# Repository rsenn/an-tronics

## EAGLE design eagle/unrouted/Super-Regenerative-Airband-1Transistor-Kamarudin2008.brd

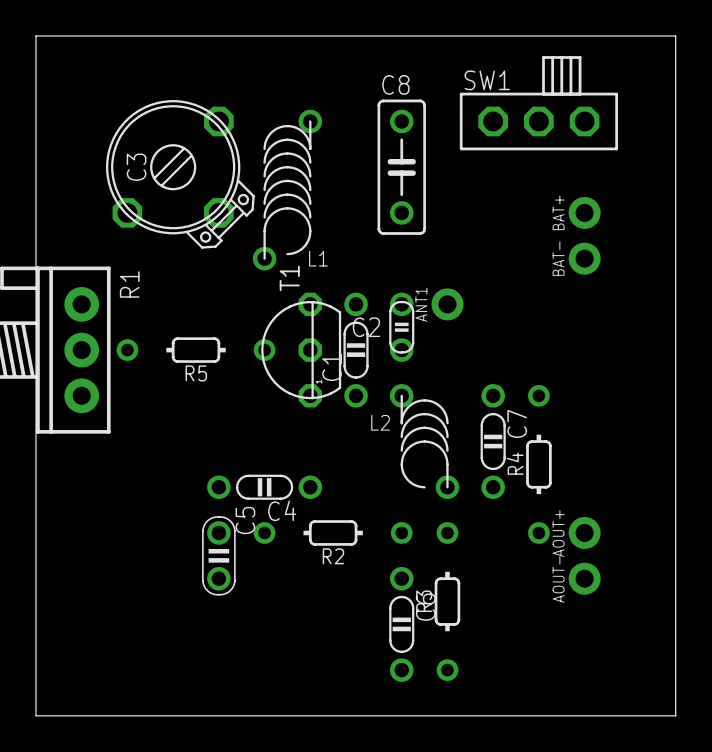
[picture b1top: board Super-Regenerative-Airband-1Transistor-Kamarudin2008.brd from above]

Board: 2 copper layers, 35.5 x 37.8 mm, 22 parts (0 on the bottom side), 12 nets, no tracks yet.

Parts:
ANT1: ANT; SPAD
AOUT+: SPAD
AOUT-: SPAD
BAT+: SPAD
BAT-: SPAD
C1: 6p; C050-020X036
C2: 2p; C025-015X024
C3: 15 - 140p; TRIM-2222-808
C4, C7: 470n; C050-020X036
C5: 1n; C025-020X036
C6: 1n; C050-020X036
C8: C050-025X075
L1: 6turns on d=0.7mm; L-04/7V-X
L2: L-SHORT02/5; L-04-5/6V
R1: 47k; POT
R2, R3: 12k; 0202/7
R4: 22k; 0202/7
R5: 68; 0202/7
SW1: SL-SW-1P-2T-H; SLSW-1P2T-H
T1: 2N3904; TO92

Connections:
GND: AOUT-.1, BAT-.1, C3.2, C5.2, C6.2, C8.2, R1.3, R3.2
unnamed: C1.2, L1.1, T1.3
unnamed: C1.1, C2.2, L2.1, T1.1
unnamed: C3.3, C8.1, L1.2, R1.1, SW1.3
unnamed: C4.2, C5.1, R5.2, T1.2
unnamed: ANT1.1, C2.1
unnamed: BAT+.1, SW1.1, SW1.2
unnamed: C4.1, R2.1
unnamed: C7.1, R4.1
unnamed: AOUT+.1, R4.2
unnamed: R1.2, R5.1
unnamed: C6.1, C7.2, L2.2, R2.2, R3.1

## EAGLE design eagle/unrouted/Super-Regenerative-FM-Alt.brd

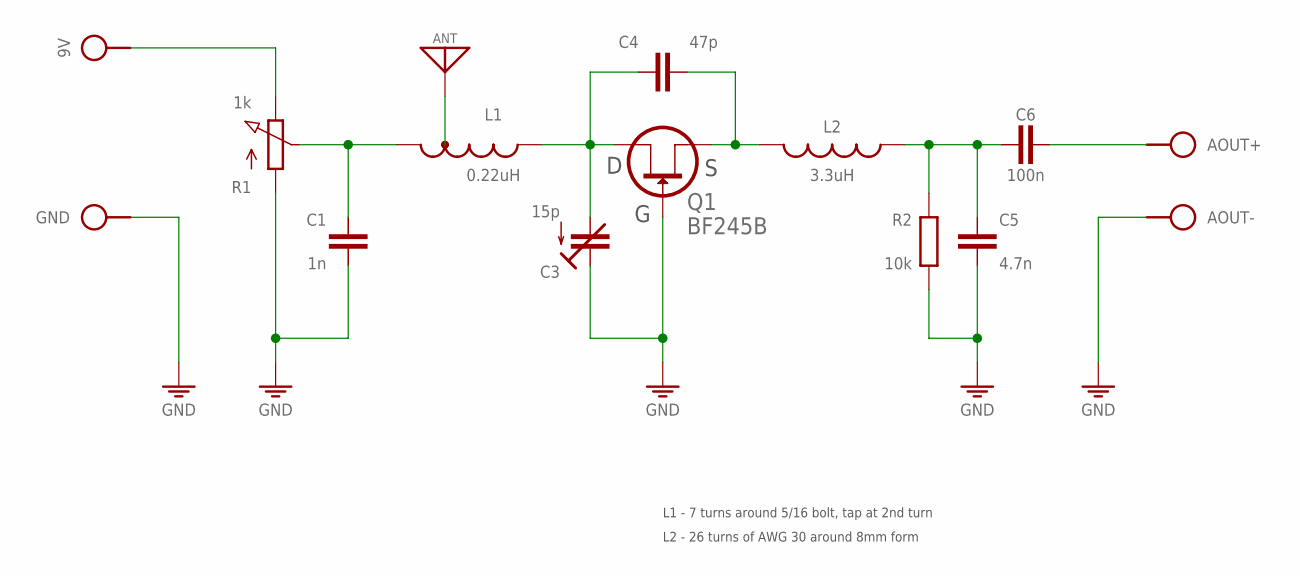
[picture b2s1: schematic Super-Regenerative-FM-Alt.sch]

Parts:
9V: SPAD
ANT: ANT; SPAD
AOUT+: SPAD
AOUT-: SPAD
C1: 1n; C050-020X036/V
C3: 15p; TRIM-2222-808
C4: 47p; C050-020X036
C5: 4.7n; C050-020X036
C6: 100n; C050-020X036
GND: SPAD
L1: 0.22uH; L-08/20V-TAP1
L2: 3.3uH; L-BODY
Q1: BF245B; TO92
R1: 1k; POT-V
R2: 10k; 0204/10

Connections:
GND: AOUT-.1, C1.2, C3.1 (E), C5.2, GND.1, Q1.1 (G), R1.A, R2.1
unnamed: 9V.1, R1.E
unnamed: C3.2 (A), C4.1, L1.2, Q1.3 (D)
unnamed: C1.1, L1.1, R1.S
unnamed: ANT.1, L1.T
unnamed: C4.2, L2.3 (2), Q1.2 (S)
unnamed: C5.1, C6.1, L2.2 (1), R2.2
unnamed: AOUT+.1, C6.2

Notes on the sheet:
L1 - 7 turns around 5/16 bolt, tap at 2nd turn
L2 - 26 turns of AWG 30 around 8mm form

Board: 2 copper layers, 15 parts (0 on the bottom side), 8 nets, no tracks yet.

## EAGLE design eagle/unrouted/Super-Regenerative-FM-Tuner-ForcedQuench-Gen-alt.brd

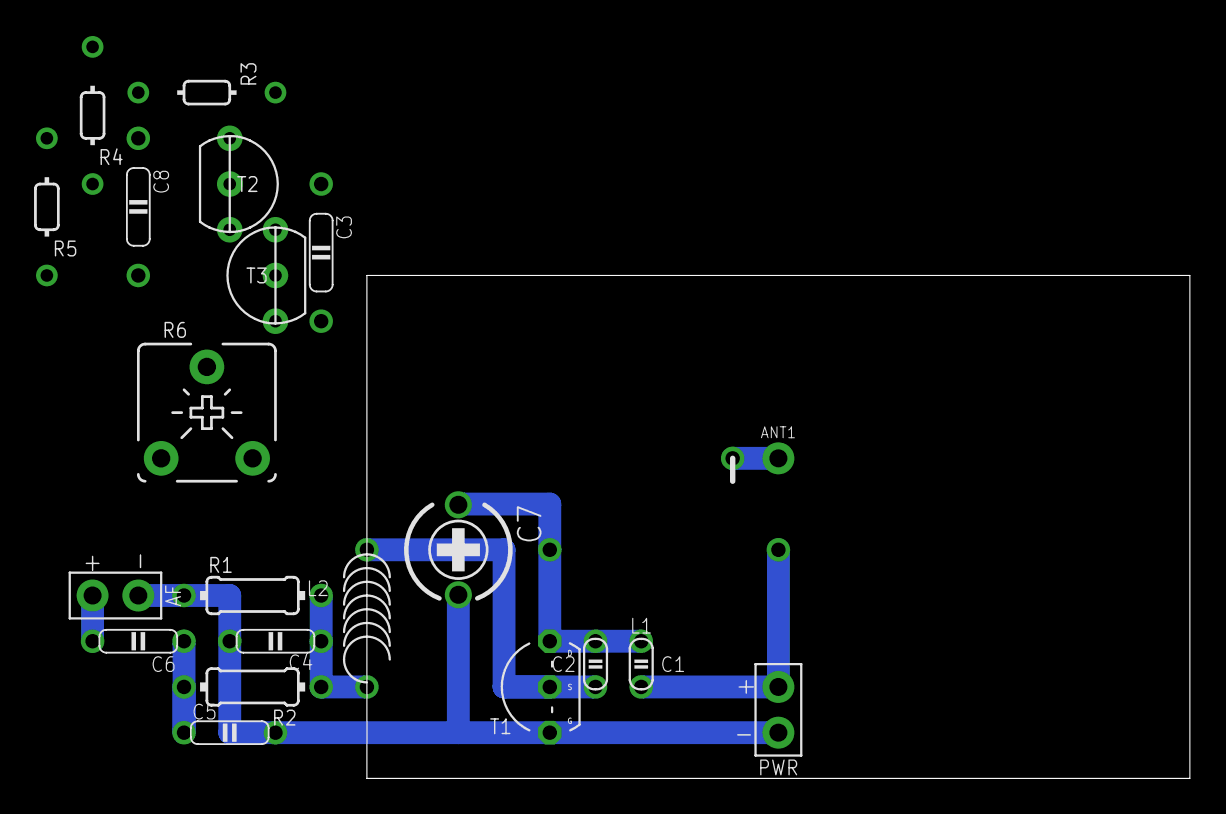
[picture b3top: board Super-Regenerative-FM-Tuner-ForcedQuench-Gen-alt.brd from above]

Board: 2 copper layers, 45.7 x 27.9 mm, 22 parts (0 on the bottom side), 12 nets.

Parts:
AF: SPAD+-+-; SPAD+-
ANT1: ANT; SPAD
C1: 20pF; C025-015X024
C2: 10pF; C025-015X024
C3, C8: 2.7nF; C0750-020X044
C4: 2.7nF; C050-020X044@1
C5: 10nF; C050-020X044@1
C6: 100nF; C050-020X044
C7: 0.04 - 6pF; CTRIMTZ03
L1: 0.1uH; L-08/12-TAP1
L2: 8.2uH; L-04/7-V
PWR: SPAD-+
R1: 10k; 0204/7
R2: 12k; 0204/7
R3: 5.1k; 0202/7-V
R4, R5: 15k; 0202/7-V
R6: 5k; POT-V
T1: BF245A; TO92-GSD
T2, T3: BC557CBE; TO92-CBE

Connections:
GND: AF.1, C4.2, C5.2, C7.1, PWR.1, R1.1, R3.1, R4.1, R5.1, R6.A, T1.1
unnamed: C1.2, C2.1, C7.2, L1.2, T1.3
unnamed: C4.1, L2.2, R1.2, R2.1
unnamed: C8.1, R3.2, T2.C
unnamed: ANT1.1, L1.3
unnamed: C2.2, L2.1, T1.2
unnamed: C5.1, C6.1, R2.2
unnamed: C8.2, R5.2, T3.B
unnamed: AF.2, C6.2
unnamed: C3.2, R6.E, T3.C
unnamed: C3.1, R4.2, T2.B
VCC: C1.1, L1.1, PWR.2, T2.E, T3.E

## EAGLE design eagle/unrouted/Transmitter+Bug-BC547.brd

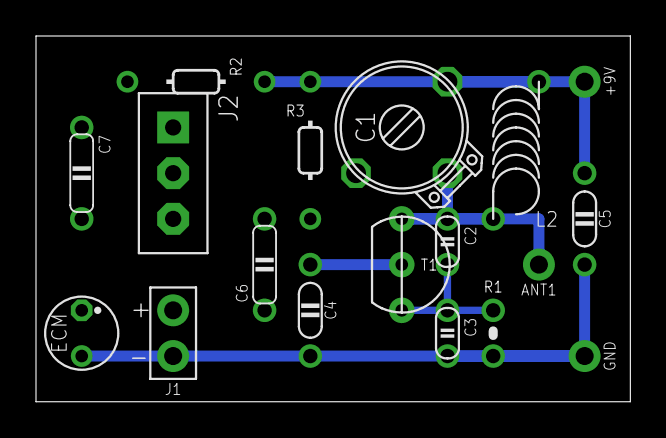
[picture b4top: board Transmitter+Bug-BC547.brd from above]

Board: 2 copper layers, 33.0 x 20.3 mm, 18 parts (0 on the bottom side), 9 nets.

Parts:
+9V: SPAD
ANT1: ANT; SPAD
C1: 1.6-15pF; TRIM-2222-808
C2: 4.7pF; C025-015X024
C3: 1nF; C025-015X024
C4: 1nF; C050-020X036/V
C5: 22nF; C050-020X036/V
C6, C7: 330nF; C050-020X044
ECM: ECM-4
GND: SPAD
J1: SPAD-+
J2: CONN-3P
L2: 1uH; L-04/7V-X
R1: 4.7; 0204/2V
R2: 4.7k; 0202/7-V
R3: 33k; 0202/7-V
T1: BC547; TO92-CBE

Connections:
+UB: +9V.1, C1.3, C5.1, L2.2, R2.1, R3.1
GND: C3.2, C4.2, C5.2, ECM.2, GND.1, J1.1, R1.2
MOD: C4.1, J2.2, R3.2, T1.B
unnamed: C6.2, J2.3
unnamed: ANT1.1, C1.2, C2.1, L2.1, T1.C
unnamed: C2.2, C3.1, R1.1, T1.E
unnamed: C7.2, J2.1
unnamed: C6.1, J1.2
unnamed: C7.1, ECM.1, R2.2

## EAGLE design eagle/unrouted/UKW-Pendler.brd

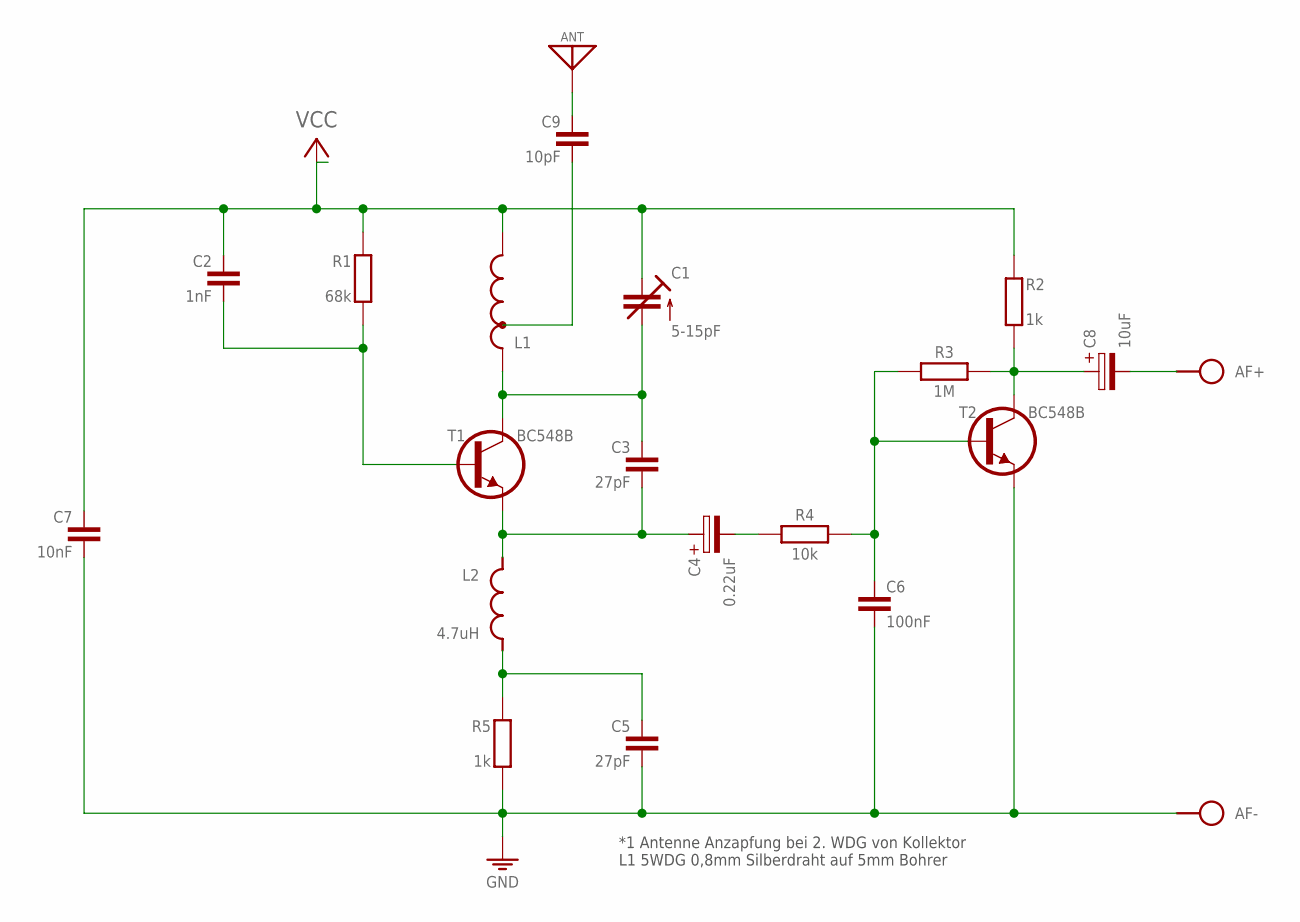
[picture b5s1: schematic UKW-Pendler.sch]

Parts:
AF: SPAD+-+-; SPAD+-
ANT: ANT; SPAD
C1: 5-15pF; TRIM-2222-808
C2: 1nF; C050-020X036/V
C3, C5: 27pF; C050-020X036/V
C4: 0.22uF; E2,5-4
C6: 100nF; C050-020X036/V
C7: 10nF; C050-020X036/V
C8: 10uF; E2,5-4
C9: 10pF; C050-020X036/V
J1: VCC_GNDPWR-L; PWR-L
L1: L-TAP104/7; L-04/10-TAP1
L2: 4.7uH; L-02/5V
R1: 68k; 0204/10-V
R2, R5: 1k; 0204/10-V
R3: 1M; 0204/10
R4: 10k; 0204/10
T1, T2: BC548B; TO92-CBE

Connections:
GND: AF.1, C5.2, C6.2, C7.2, J1.1 (GND), R5.2, T2.E
unnamed: ANT.1, C9.1
unnamed: C3.2, C4.+, L2.2, T1.E
unnamed: C1.2 (A), C3.1, L1.1, T1.C
unnamed: C4.-, R4.2
unnamed: C6.1, R3.2, R4.1, T2.B
unnamed: C5.1, L2.1, R5.1
unnamed: C2.2, R1.2, T1.B
unnamed: C8.+, R2.2, R3.1, T2.C
unnamed: AF.2, C8.-
unnamed: C9.2, L1.T
unnamed: C1.3 (E), C2.1, C7.1, L1.2, R1.1, R2.1

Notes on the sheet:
*1 Antenne Anzapfung bei 2. WDG von Kollektor L1 5WDG 0,8mm Silberdraht auf 5mm Bohrer

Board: 2 copper layers, 21 parts (0 on the bottom side), 12 nets, no tracks yet.

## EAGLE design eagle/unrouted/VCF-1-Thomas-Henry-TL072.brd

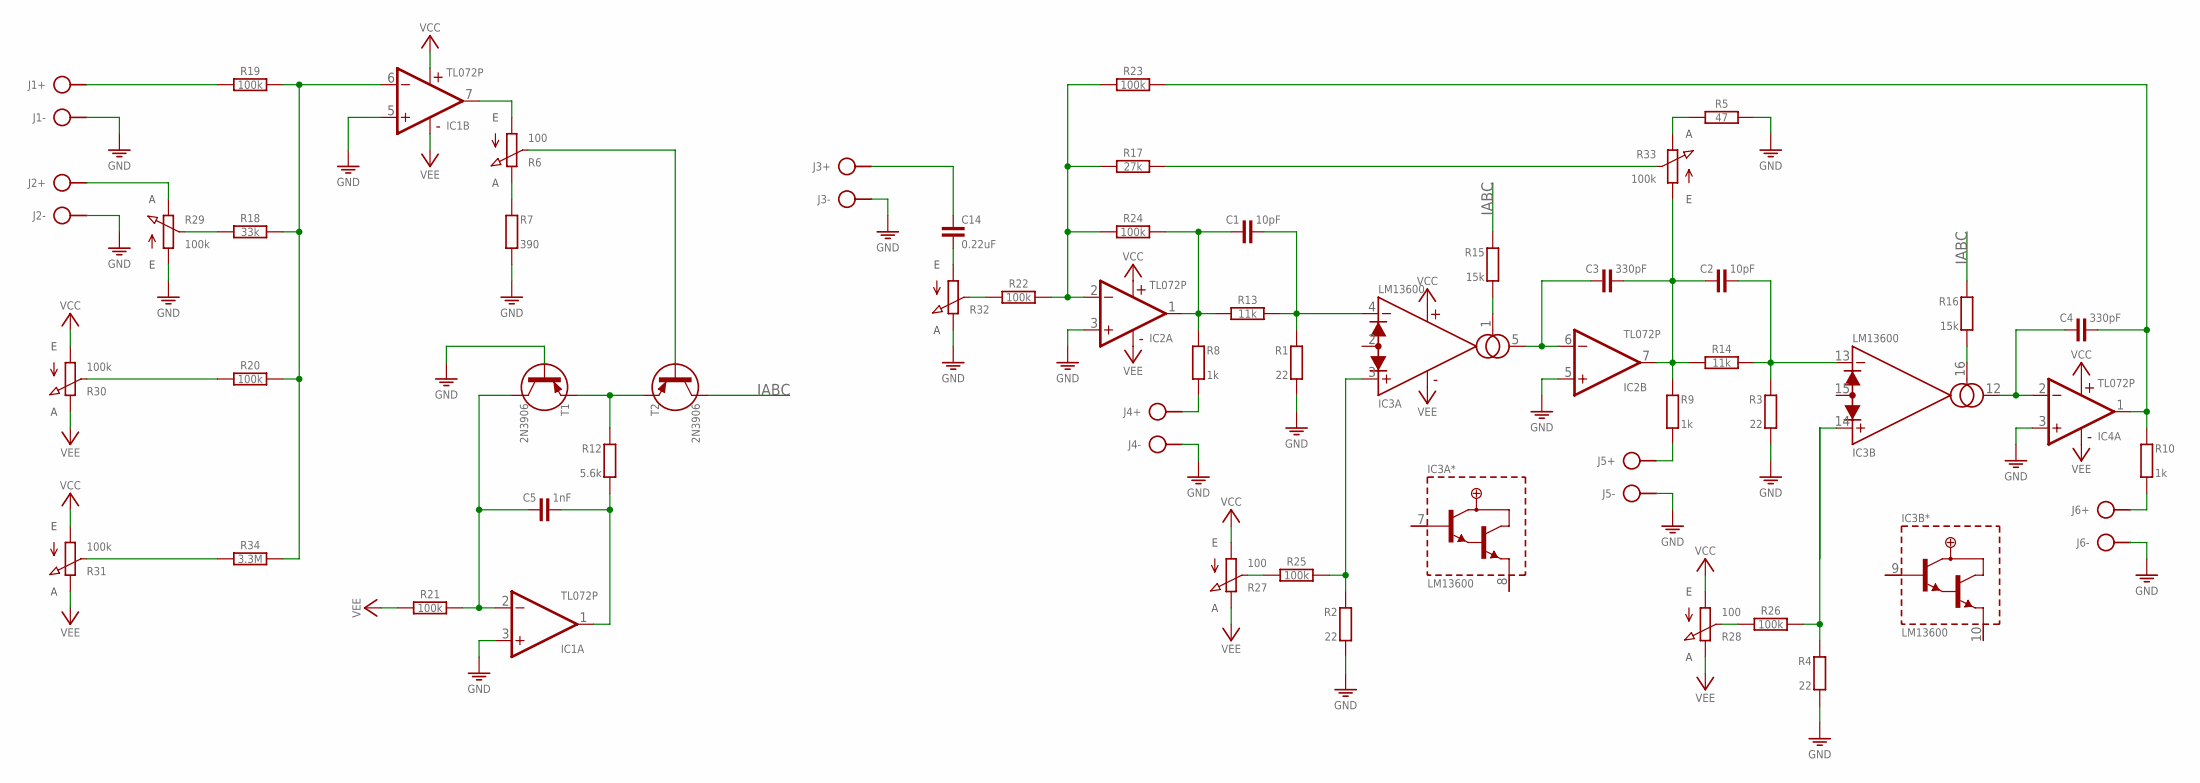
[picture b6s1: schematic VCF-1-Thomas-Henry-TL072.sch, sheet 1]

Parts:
C1, C2: 10pF; C050-020X036
C3, C4: 330pF; C050-020X036
C5: 1nF; C050-020X036
C14: 0.22uF; C050-020X044/V
IC1, IC2, IC4: TL072P; DIL08
IC3: LM13600; DIL16
J1: 1V/Oct; SPAD-+
J2: Envelope; SPAD-+
J3: AUDIO INPUT; SPAD-+
J4: HIGH PASS; SPAD+-
J5: BAND PASS; SPAD-+
J6: LOW PASS; SPAD-+
R1, R2, R3, R4: 22; 0204/10-V
R5: 47; 0204/10
R6, R27, R28: 100; POT-V
R7: 390; 0204/10-V
R8, R9, R10: 1k; 0204/10-V
R12: 5.6k; 0204/10-V
R13, R14: 11k; 0204/10
R15, R16: 15k; 0204/10-V
R17: 27k; 0204/10
R18: 33k; 0204/10
R19, R20, R21, R22, R23, R24, R25, R26: 100k; 0204/10
R29, R30, R31, R33: 100k; POT
R32: POT
R34: 3.3M; 0204/10
T1, T2: 2N3906; TO92

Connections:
GND: IC1.3 (+IN), IC1.5 (+IN), IC2.3 (+IN), IC2.5 (+IN), IC4.3 (+IN), J1.1, J2.1, J3.1, J4.1, J5.1, J6.1, R1.2, R2.2, R3.2, R4.2, R5.2, R7.2, R29.1 (A), R32.3 (E), T1.2 (B)
IABC: R15.1, R16.1, T2.3 (C)
unnamed: J1.2, R19.1
unnamed: R18.1, R29.2 (S)
unnamed: J2.2, R29.3 (E)
unnamed: R20.1, R30.2 (S)
unnamed: R31.2 (S), R34.1
unnamed: IC1.6 (-IN), R18.2, R19.2, R20.2, R34.2
unnamed: IC1.7 (OUT), R6.A
unnamed: R6.E, R7.1
unnamed: R12.1, T1.1 (E), T2.1 (E)
unnamed: C5.2, IC1.1 (OUT), R12.2
unnamed: C5.1, IC1.2 (-IN), R21.2, T1.3 (C)
unnamed: R6.S, T2.2 (B)
unnamed: R22.1, R32.2 (S)
unnamed: IC2.2 (-IN), R17.1, R22.2, R23.1, R24.1
unnamed: C1.1, IC2.1 (OUT), R8.1, R13.1, R24.2
unnamed: C1.2, IC3.4 (-IN), R1.1, R13.2
unnamed: J4.2, R8.2
unnamed: IC3.1 (AMP/BIAS), R15.2
unnamed: C3.1, IC2.6 (-IN), IC3.5 (OUT)
unnamed: C2.1, C3.2, IC2.7 (OUT), R9.1, R14.1, R33.1 (A)
unnamed: J5.2, R9.2
unnamed: C2.2, IC3.13 (-IN), R3.1, R14.2
unnamed: R25.1, R27.S
unnamed: IC3.3 (+IN), R2.1, R25.2
unnamed: R26.1, R28.S
unnamed: R4.1, R26.2
unnamed: IC3.16 (AMP/BIAS), R16.2
unnamed: C4.1, IC3.12 (OUT), IC4.2 (-IN)
unnamed: C4.2, IC4.1 (OUT), R10.1, R23.2
unnamed: J6.2, R10.2
unnamed: R17.2, R33.2 (S)
unnamed: R5.1, R33.3 (E)
unnamed: C14.1, J3.2
unnamed: C14.2, R32.1 (A)
VCC: IC1.8 (V+), IC2.8 (V+), IC3.11 (V+), IC4.8 (V+), R27.A, R28.A, R30.1 (A), R31.1 (A)
VEE: IC1.4 (V-), IC2.4 (V-), IC3.6 (V-), IC4.4 (V-), R21.1, R27.E, R28.E, R30.3 (E), R31.3 (E)

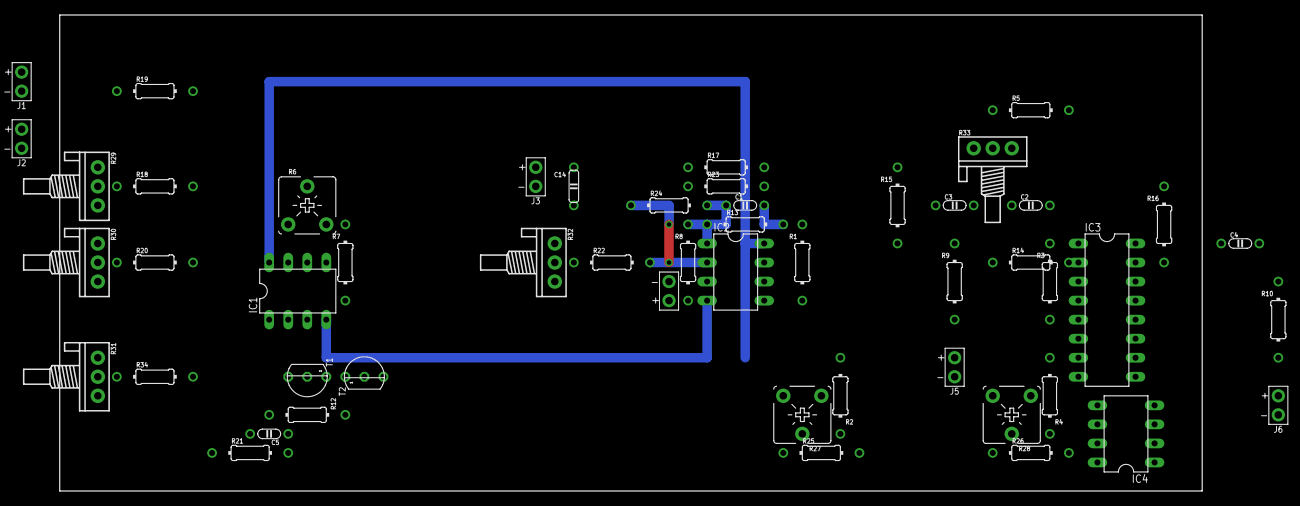
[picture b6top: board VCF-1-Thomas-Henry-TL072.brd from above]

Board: 2 copper layers, 152.4 x 63.5 mm, 51 parts (0 on the bottom side), 38 nets.
